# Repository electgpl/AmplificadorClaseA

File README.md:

# Amplificador de Audio en Clase A

Este proyecto se trata de un amplificador de audio de potencia en clase A.
Existen muchas Clases de amplificación, que responden a distintas topologias y tecnologías de diseño.
Las mas comunes en Audio hoy en día son la Clase AB y la Clase D, siendo la mas antigua la clase AB, aunque la Clase A también es antigua pero tiene algunos pros y contra respecto a las demás clases de amplificador.

## Pros:

  - No posee distorsión por cruce, esta existe en todos los Clase AB.
  - No posee fuentes de ruido, esta existe en todos los Clase D.
  - Distorsión Harmónica Total reducida, aquí depende del diseño, pero es muy baja.
  - Ancho de banda mayor de respuesta en frecuencia
  
## Contras:

  - Un bajo rendimiento de energía, al rededor del 30%, (ejemplo: 10W de consumo, 3W de salida).
  - Exceso de Temperatura, de la mano del rendimiento, mucha energía disipada en calor.
  - Fuentes de alimentación costosas, Se requiere de fuentes bien filtradas y de potencia.

## Circuito

Como podemos ver, el circuito posee muy pocos componentes, tenemos remarcado en Amarillo el transistor que se encarga de generar una fuente de corriente constante, y en Azul los transistores que se encargan de amplificar el Audio.
Ambos transistores de potencia son TIP3055, son algo grandes, pero por la relación precio producto, vamos a trabajar holgados en cuanto a potencia de disipación y nuestro amplificador tendrá mejor performance.
Tenemos una etapa principal que es un preamplificador en base al 2N3906, luego este excita el driver de potencia en base al BD135 y por ultimo este alimenta la base de potencia del TIP3055, con esto conformamos las veces de amplificación del circuito.
Como fuente de corriente CCR, tenemos otro TIP3055 junto a la polarizacion directa, podremos lograr al rededor de 1A de corriente constante.
Es necesario dotar estos transistores de buenos disipadores de calor.

## Analisis

Analizamos este circuito en LTSpice y podremos ver la respuesta en frecuencia que arranca desde los 4Hz y termina casi en 100kHz, esto nos proporciona un ancho de banda bastante grande y nos asegura una buena respuesta en frecuencia de nuestro amplificador para trabajar en todo el rango de audio 20Hz a 20kHz.

## Diseño

> Diseñado con EAGLE, en solo dos capas con componentes THT para facilitar
> la integración al alumno, el desarrollo del PCB en el hogar y mantener
> el menor costo posible.

Patrocinado
----
¿Dónde fabricamos nuestros PCBs?
Nuestros PCBs los fabricamos con la empresa PCBWay, esta empresa nos permite realizar pequeñas cantidades como prototipos rápidos para nuestros desarrollos a medida.
También nos permite realizar grandes producciones para realizar proyectos comerciales.
Servicio de prototipo de PCB por tan solo $5 las 10 unidades.
Cada nuevo miembro recibirá un bono de $5, más servicio express de 24Hs o 48Hs.
Servicio de ensamblado de PCB por $88 más envió gratis en todo el mundo, más esténcil, más componentes.
Un servicio de calidad!
https://www.pcbway.es/

License
----

MIT

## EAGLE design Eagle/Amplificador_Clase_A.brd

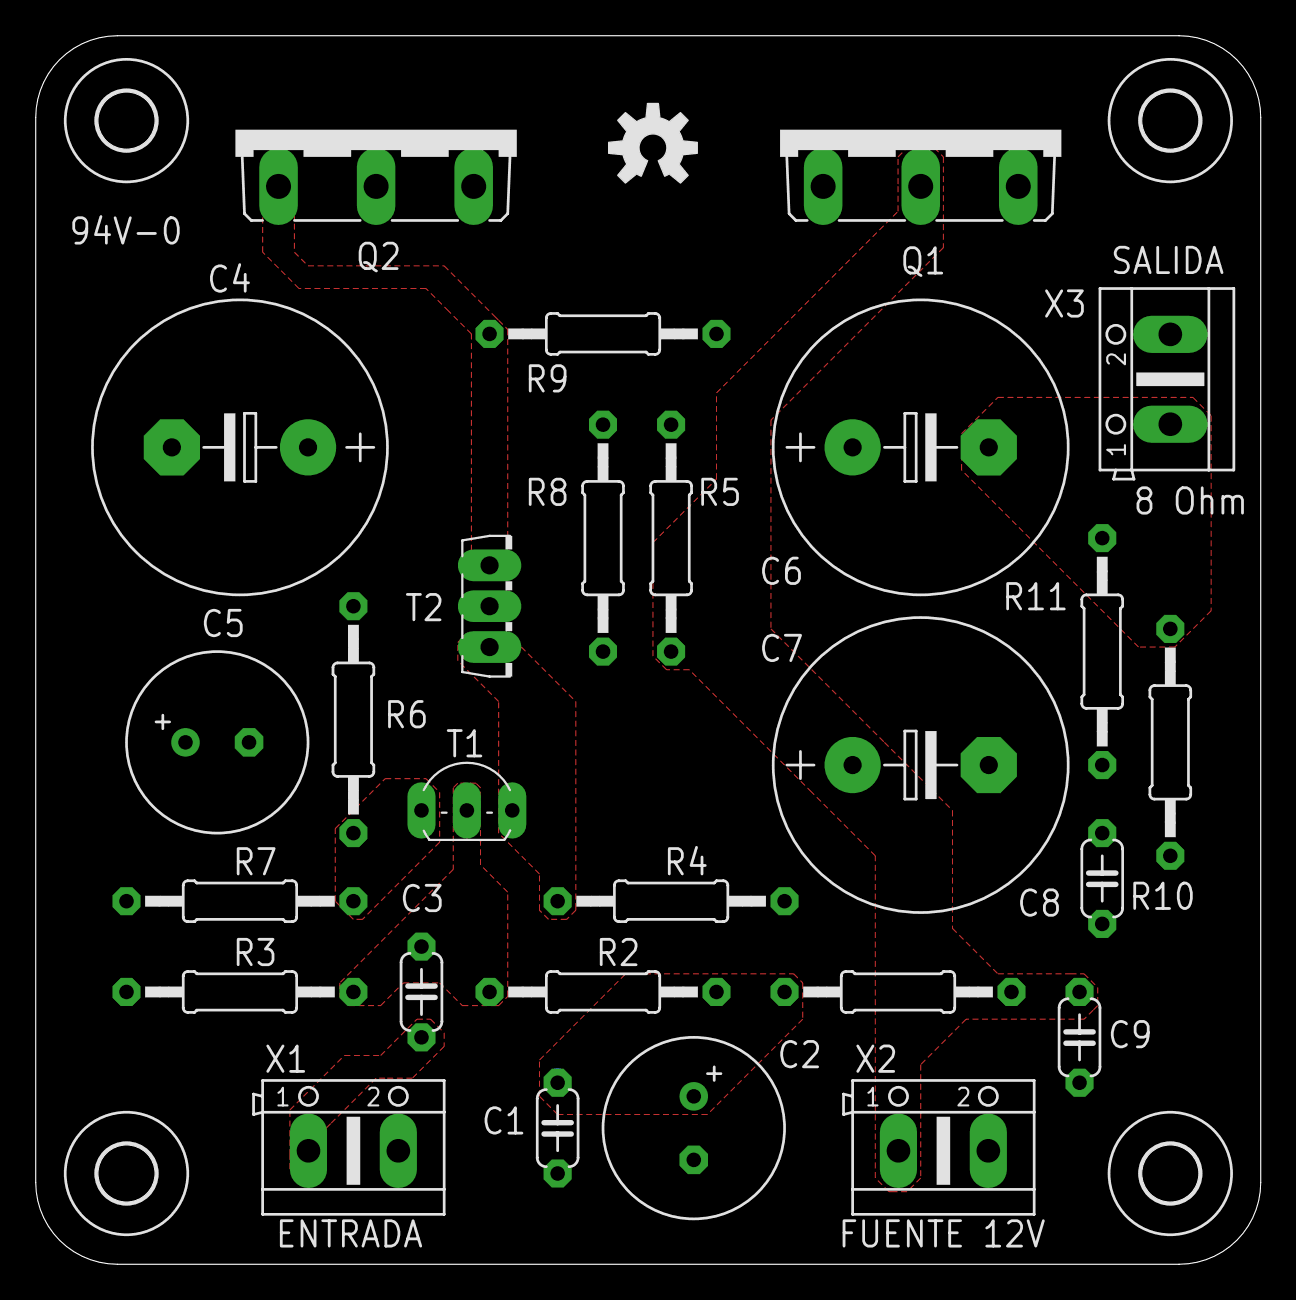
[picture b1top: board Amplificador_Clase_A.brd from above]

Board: 2 copper layers, 68.6 x 68.8 mm, 32 parts (0 on the bottom side), 14 nets.

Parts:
C1, C8, C9: 100n; C050-024X044
C2: 100u; E3,5-10
C3: 470n; C050-024X044
C4: 470u; E7,5-16
C5: 220u; E3,5-10
C6, C7: 4700u; E7,5-16
LOGO1: OSHW-LOGOM; OSHW-LOGO-M
Q1, Q2: TIP3055; TOP3AV
R1: 47k; 0207/12
R2, R3: 100k; 0207/12
R4, R10: 10k; 0207/12
R5: 47R; 0207/12
R6: 2k7; 0207/12
R7, R8: 220R; 0207/12
R9: 2k2; 0207/12
R11: 4R7; 0207/12
T1: 2N3906; TO92-EBC
T2: BC639; TO126V
U$1, U$2, U$3, U$4: 3,2
X1, X2, X3: AK500/2

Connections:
+12V: C7.+, C9.1, Q1.C, R1.2, R5.2, X2.1
GND: C1.2, C2.-, C5.-, C7.-, C8.2, C9.2, Q2.E, R3.1, R4.1, R9.2, R10.2, X1.2, X2.2, X3.2
unnamed: C3.2, R2.1, R3.2, T1.B
unnamed: C1.1, C2.+, R1.1, R2.2
unnamed: R4.2, T1.C, T2.3
unnamed: C5.+, R7.1
unnamed: R6.1, R7.2, T1.E
unnamed: C4.-, C6.+, Q1.E, Q2.C, R6.2
unnamed: C4.+, R5.1, R8.2
unnamed: Q1.B, R8.1, T2.2
unnamed: Q2.B, R9.1, T2.1
unnamed: C3.1, X1.1
unnamed: C6.-, R10.1, R11.1, X3.1
unnamed: C8.1, R11.2

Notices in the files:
parts and their libraries:
SparkFun-Aesthetics: Licensing: Creative Commons ShareAlike 4.0 International - https://creativecommons.org/licenses/by-sa/4.0
